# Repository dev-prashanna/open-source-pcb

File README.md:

# Open Source PCB

Open hardware designs for ESP32 robotics, a brushed-motor flight controller, and a USB logic analyser.

## LogicScope S3

[LogicScope S3](LogicScope_S3/) is a compact 8-channel USB digital logic analyser hardware prototype built around the ESP32-S3, with a 55 x 40-mm, two-layer PCB.

- [Project documentation](LogicScope_S3/README.md)
- [KiCad project](LogicScope_S3/LogicScope_S3.kicad_pro)
- [Fabrication and assembly package](LogicScope_S3/fabrication/)
- [Engineering report](LogicScope_S3/docs/Engineering_Report.md)
- [Hardware validation plan](LogicScope_S3/docs/Validation_Plan.md)
- [License](LogicScope_S3/LICENSE)

LS-S3-A0 has recorded passing ERC, DRC, connectivity and schematic/PCB parity checks. Firmware and a simple desktop app v0.1.0 are implemented, with finite DMA captures, an eight-channel viewer, timing cursors and CSV/VCD export. Sampling performance and electrical behavior require physical prototype validation.

- [Firmware: build and flash](LogicScope_S3/firmware/README.md)
- [Desktop app: install and demo](LogicScope_S3/software/README.md)
- [Software verification](LogicScope_S3/docs/Software_Verification.md)

## RoveFlight S3

[RoveFlight S3](RoveFlight_S3/) is a 45 x 45-mm, six-layer ESP32-S3 controller for a 1S brushed quadcopter, with hardware motor interlocks, IMU, barometer, ToF and expansion interfaces.

- [Project documentation](RoveFlight_S3/README.md)
- [KiCad project](RoveFlight_S3/RoveFlight_S3.kicad_pro)
- [Fabrication and assembly package](RoveFlight_S3/fabrication/)
- [Manufacturing readiness and validation](RoveFlight_S3/docs/Manufacturing_Readiness.md)
- [License](RoveFlight_S3/LICENSE)

RF-S3-A0 passes ERC, DRC, connectivity and schematic/PCB parity checks. Via filling/capping and fabricator DFM are required; bench and flight qualification remain open.

## RoveCore One

The complete ESP32 robotics PCB project is in [RoveCore](RoveCore/).

- [Project documentation](RoveCore/README.md)
- [KiCad project](RoveCore/RoveCore_One.kicad_pro)
- [Fabrication files](RoveCore/fabrication/)
- [Manufacturing readiness](RoveCore/docs/Manufacturing_Readiness.md)
- [License](RoveCore/LICENSE)

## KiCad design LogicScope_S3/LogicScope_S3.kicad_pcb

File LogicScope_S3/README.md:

# LogicScope S3 — LS-S3-A0

Compact 8-channel USB digital logic analyzer hardware by Prashanna Tiwari.
Open `LogicScope_S3.kicad_pro` in KiCad 10. The project contains native
hierarchical schematics, verified library parts and an actual two-layer PCB.

**Engineering prototype; firmware and desktop software v0.1.0 are implemented
but not bench validated.** 1 MS/s is an unmeasured finite-capture target,
not an advertised continuous rate. There is no analog voltage measurement.

## Design

- ESP32-S3-WROOM-1-N8R2, eight parallel LCD_CAM inputs and GDMA.
- SN74LVC245APW at 3.3 V with 5.5-V-tolerant inputs, 220-ohm series resistors
  and 100-kilohm input pull-downs. External signal range: 0–5 V.
- USB-C device port, native USB Full-Speed, ESD protection and 3.3-V buck supply.
- Two 2x5 input headers, BOOT/RESET, capture/power LEDs and UART/test access.
- 55 x 40 mm, two layers, 0.8-mm board; PCB antenna overhangs by 6.75 mm.
- **TIWARI** etched in front copper and printed on silkscreen.

Use a common ground with the target. J2 pin 7 is a current-limited reference
only; this instrument does not power the target.

## Firmware and desktop software

- [ESP32-S3 firmware: build, flash and capture behavior](firmware/README.md)
- [Simple desktop app: setup and usage](software/README.md)
- [USB protocol](docs/USB_Protocol.md)
- [Software verification and remaining hardware checks](docs/Software_Verification.md)

Firmware uses LCD_CAM/GDMA with the PCB's GPIO12-to-GPIO11 sampling-clock
loopback. Select 100 kS/s, 250 kS/s, 500 kS/s or 1 MS/s and collect up to
65,536 packed eight-channel samples before uploading over USB. All rates
remain unmeasured. Trigger search marks a matching event within a finite
capture; rolling pre-trigger history and continuous streaming are not enabled.

The Python/Tk app includes eight waveform lanes, zoom/pan, timing cursors,
save/open, CSV/VCD export, and a synthetic demo mode. From `software/`:

```sh
python3 -m venv .venv
. .venv/bin/activate
python -m pip install -e .
logicscope --demo
```

## Files and limitations

Read [acquisition architecture](docs/Acquisition_Architecture.md),
[electrical/fabrication decisions](docs/Electrical_and_Fabrication.md) and the
[hardware validation plan](docs/Validation_Plan.md) before ordering or using
a prototype. Connector pinout and GPIO allocation are supplied as CSV files.
`BOM.csv` contains exact manufacturer part numbers and DNP status.

Final checks: ERC 0, DRC 0, unconnected nets 0, schematic parity findings 0.
Read the [engineering report](docs/Engineering_Report.md). Manufacturing files
are in `fabrication/`; the KiCad 3D render is in `previews/`.

Fabrication needs a stack-specific USB impedance review and the documented
USB connector hole-clearance capability. Sampling, USB throughput, power,
thermal and ESD behavior require physical prototype testing.

## Tool workflow

Connected KiCad MCP created the native project and initial components,
generated a netlist and ran electrical checks. Native pcbnew scripts perform
placement and routing because those editing operations are absent from the
connected MCP. Native KiCad CLI and MCP perform final validation and exports.
Scripts under `scripts/` record engineering operations; do not run placement
or initial-routing scripts over the completed board. `release.py`, when
available, validates the current design and exports without reconstructing it.

Copyright (c) 2026 Prashanna Tiwari. Hardware: [CERN-OHL-P-2.0](LICENSE).
Firmware and desktop app: MIT (see their respective directories).
KiCad-derived library graphics retain their upstream licence in `libraries/`.

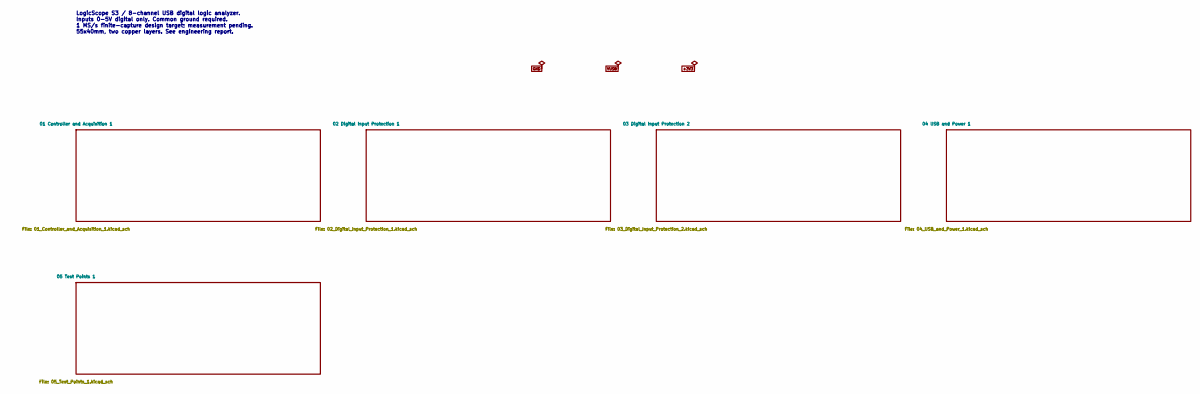
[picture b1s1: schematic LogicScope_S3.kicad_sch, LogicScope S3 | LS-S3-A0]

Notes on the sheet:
LogicScope S3 / 8-channel USB digital logic analyzer. Inputs 0-5V digital only. Common ground required. 1 MS/s finite-capture design target; measurement pending. 55x40mm, two copper layers. See engineering report.

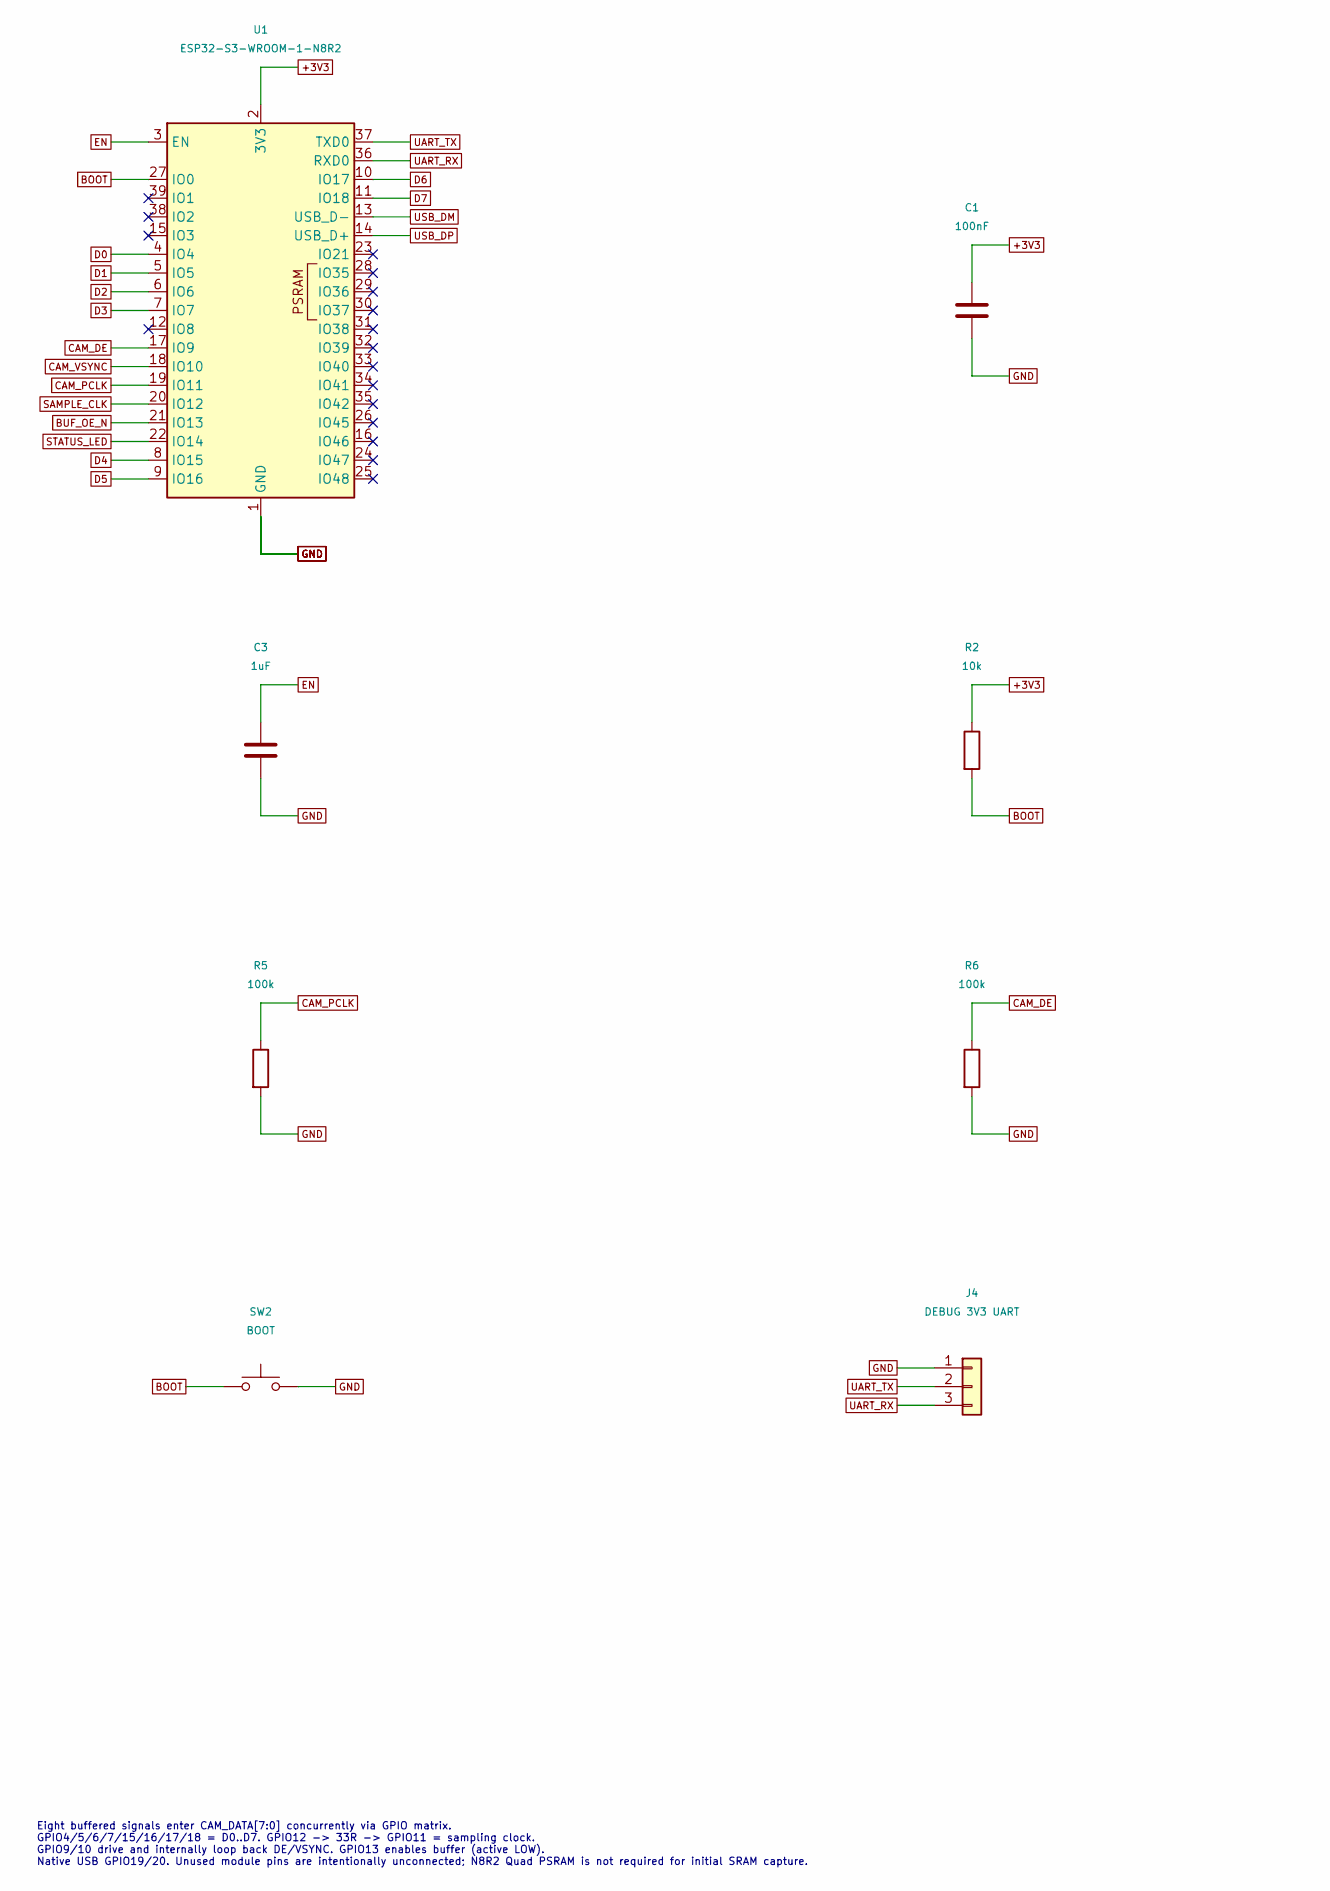
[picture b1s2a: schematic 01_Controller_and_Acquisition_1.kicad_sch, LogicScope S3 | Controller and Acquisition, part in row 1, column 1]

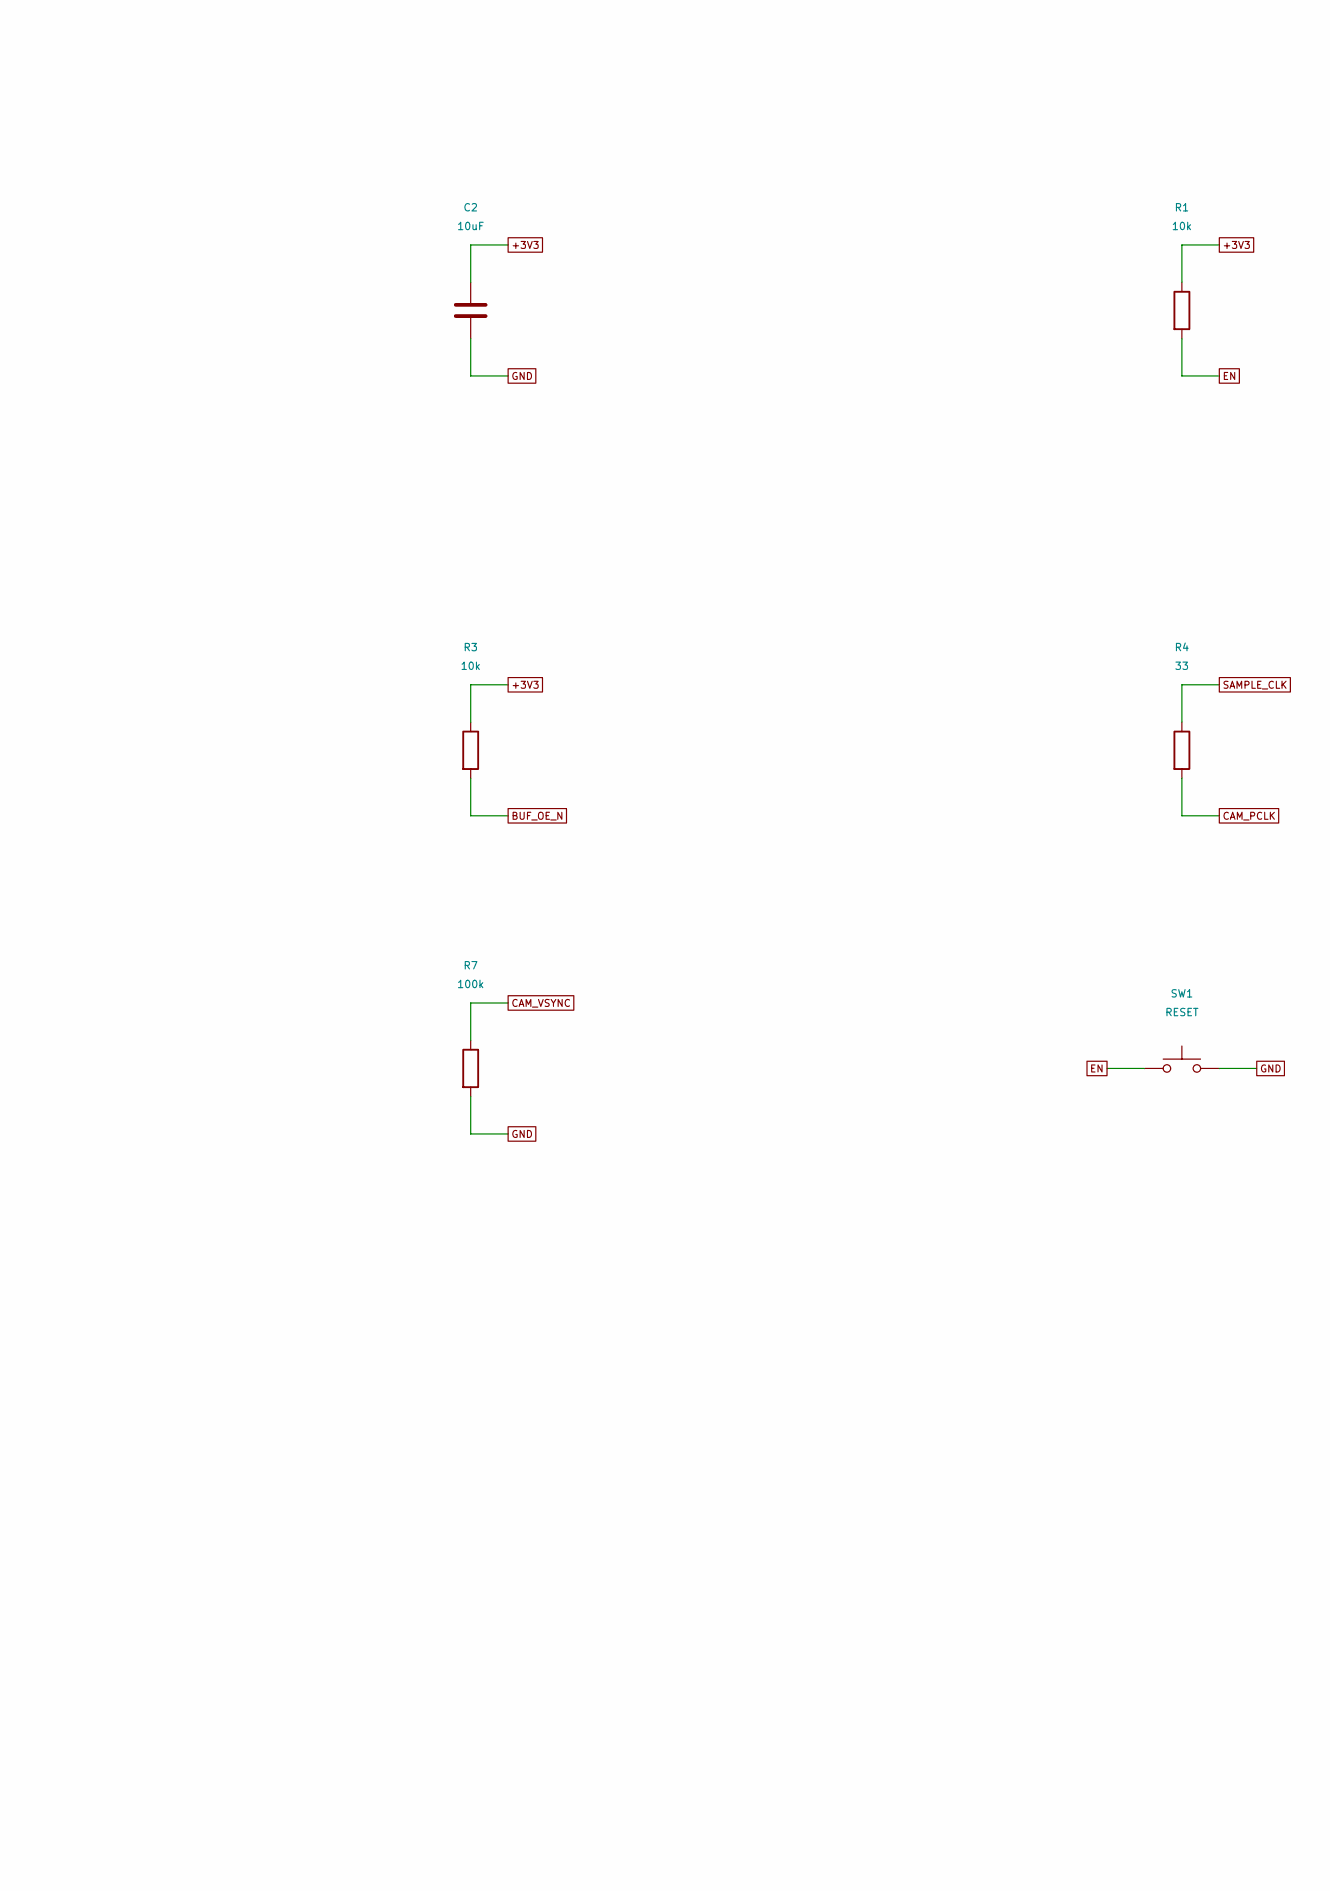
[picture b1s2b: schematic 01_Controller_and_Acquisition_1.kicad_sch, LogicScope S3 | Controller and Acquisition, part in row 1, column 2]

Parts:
C1: 100nF; C_0603_1608Metric; MPN GRM188R71C104KA01D
C2: 10uF; C_0805_2012Metric; MPN GRM21BR61A106KE19L
C3: 1uF; C_0603_1608Metric; MPN GRM188R61A105KA61D
J4: DEBUG 3V3 UART; PinHeader_1x03_P2.54mm_Vertical; MPN 61300311121
R1, R2, R3: 10k; R_0603_1608Metric; MPN RC0603FR-0710KL
R4: 33; R_0603_1608Metric; MPN RC0603FR-0733RL
R5, R6, R7: 100k; R_0603_1608Metric; MPN RC0603FR-07100KL
SW1: RESET; SW_Push_1P1T-SH_NO_CK_KMR2xxG; MPN KMR221GLFS
SW2: BOOT; SW_Push_1P1T-SH_NO_CK_KMR2xxG; MPN KMR221GLFS
U1: ESP32-S3-WROOM-1-N8R2; ESP32-S3-WROOM-1_Overhang; MPN ESP32-S3-WROOM-1-N8R2

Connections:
+3V3: C1.1, C2.1, R1.1, R2.1, R3.1, U1.2 (3V3); also elsewhere on the board
BOOT: R2.2, SW2.1, U1.27 (IO0)
BUF_OE_N: R3.2, U1.21 (IO13); also elsewhere on the board
CAM_DE: R6.1, U1.17 (IO9); also elsewhere on the board
CAM_PCLK: R4.2, R5.1, U1.19 (IO11); also elsewhere on the board
CAM_VSYNC: R7.1, U1.18 (IO10); also elsewhere on the board
D0: U1.4 (IO4); also elsewhere on the board
D1: U1.5 (IO5); also elsewhere on the board
D2: U1.6 (IO6); also elsewhere on the board
D3: U1.7 (IO7); also elsewhere on the board
D4: U1.8 (IO15); also elsewhere on the board
D5: U1.9 (IO16); also elsewhere on the board
D6: U1.10 (IO17); also elsewhere on the board
D7: U1.11 (IO18); also elsewhere on the board
EN: C3.1, R1.2, SW1.1, U1.3 (EN); also elsewhere on the board
GND: C1.2, C2.2, C3.2, J4.1, R5.2, R6.2, R7.2, SW1.2, SW2.2, U1.1 (GND), U1.40 (GND), U1.41 (GND); also elsewhere on the board
SAMPLE_CLK: R4.1, U1.20 (IO12)
STATUS_LED: U1.22 (IO14); also elsewhere on the board
UART_RX: J4.3, U1.36 (RXD0)
UART_TX: J4.2, U1.37 (TXD0)
USB_DM: U1.13 (USB_D-); also elsewhere on the board
USB_DP: U1.14 (USB_D+); also elsewhere on the board

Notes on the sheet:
Eight buffered signals enter CAM_DATA[7:0] concurrently via GPIO matrix. GPIO4/5/6/7/15/16/17/18 = D0..D7. GPIO12 -> 33R -> GPIO11 = sampling clock. GPIO9/10 drive and internally loop back DE/VSYNC. GPIO13 enables buffer (active LOW). Native USB GPIO19/20. Unused module pins are intentionally uncon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

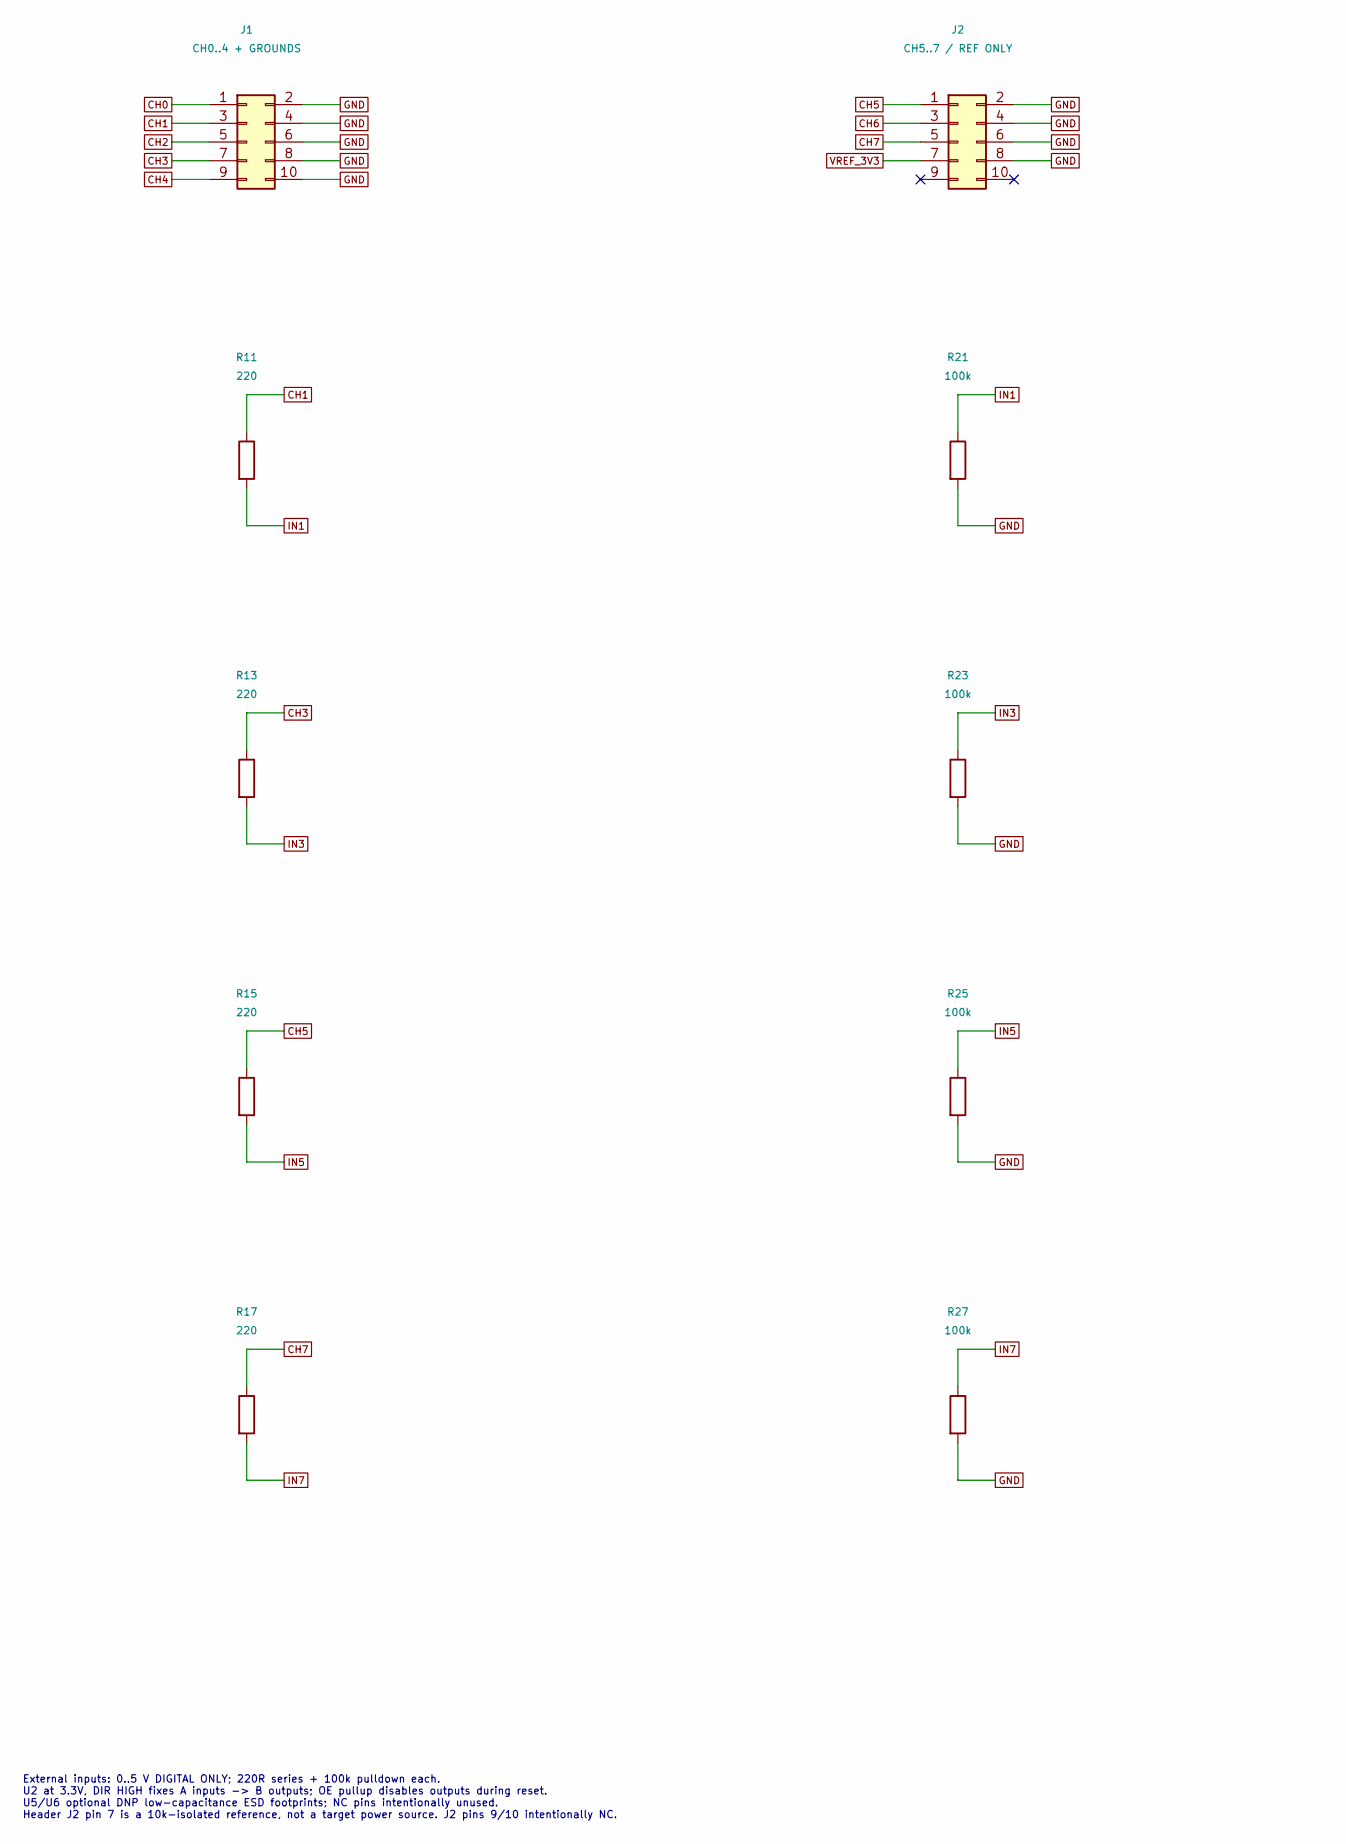
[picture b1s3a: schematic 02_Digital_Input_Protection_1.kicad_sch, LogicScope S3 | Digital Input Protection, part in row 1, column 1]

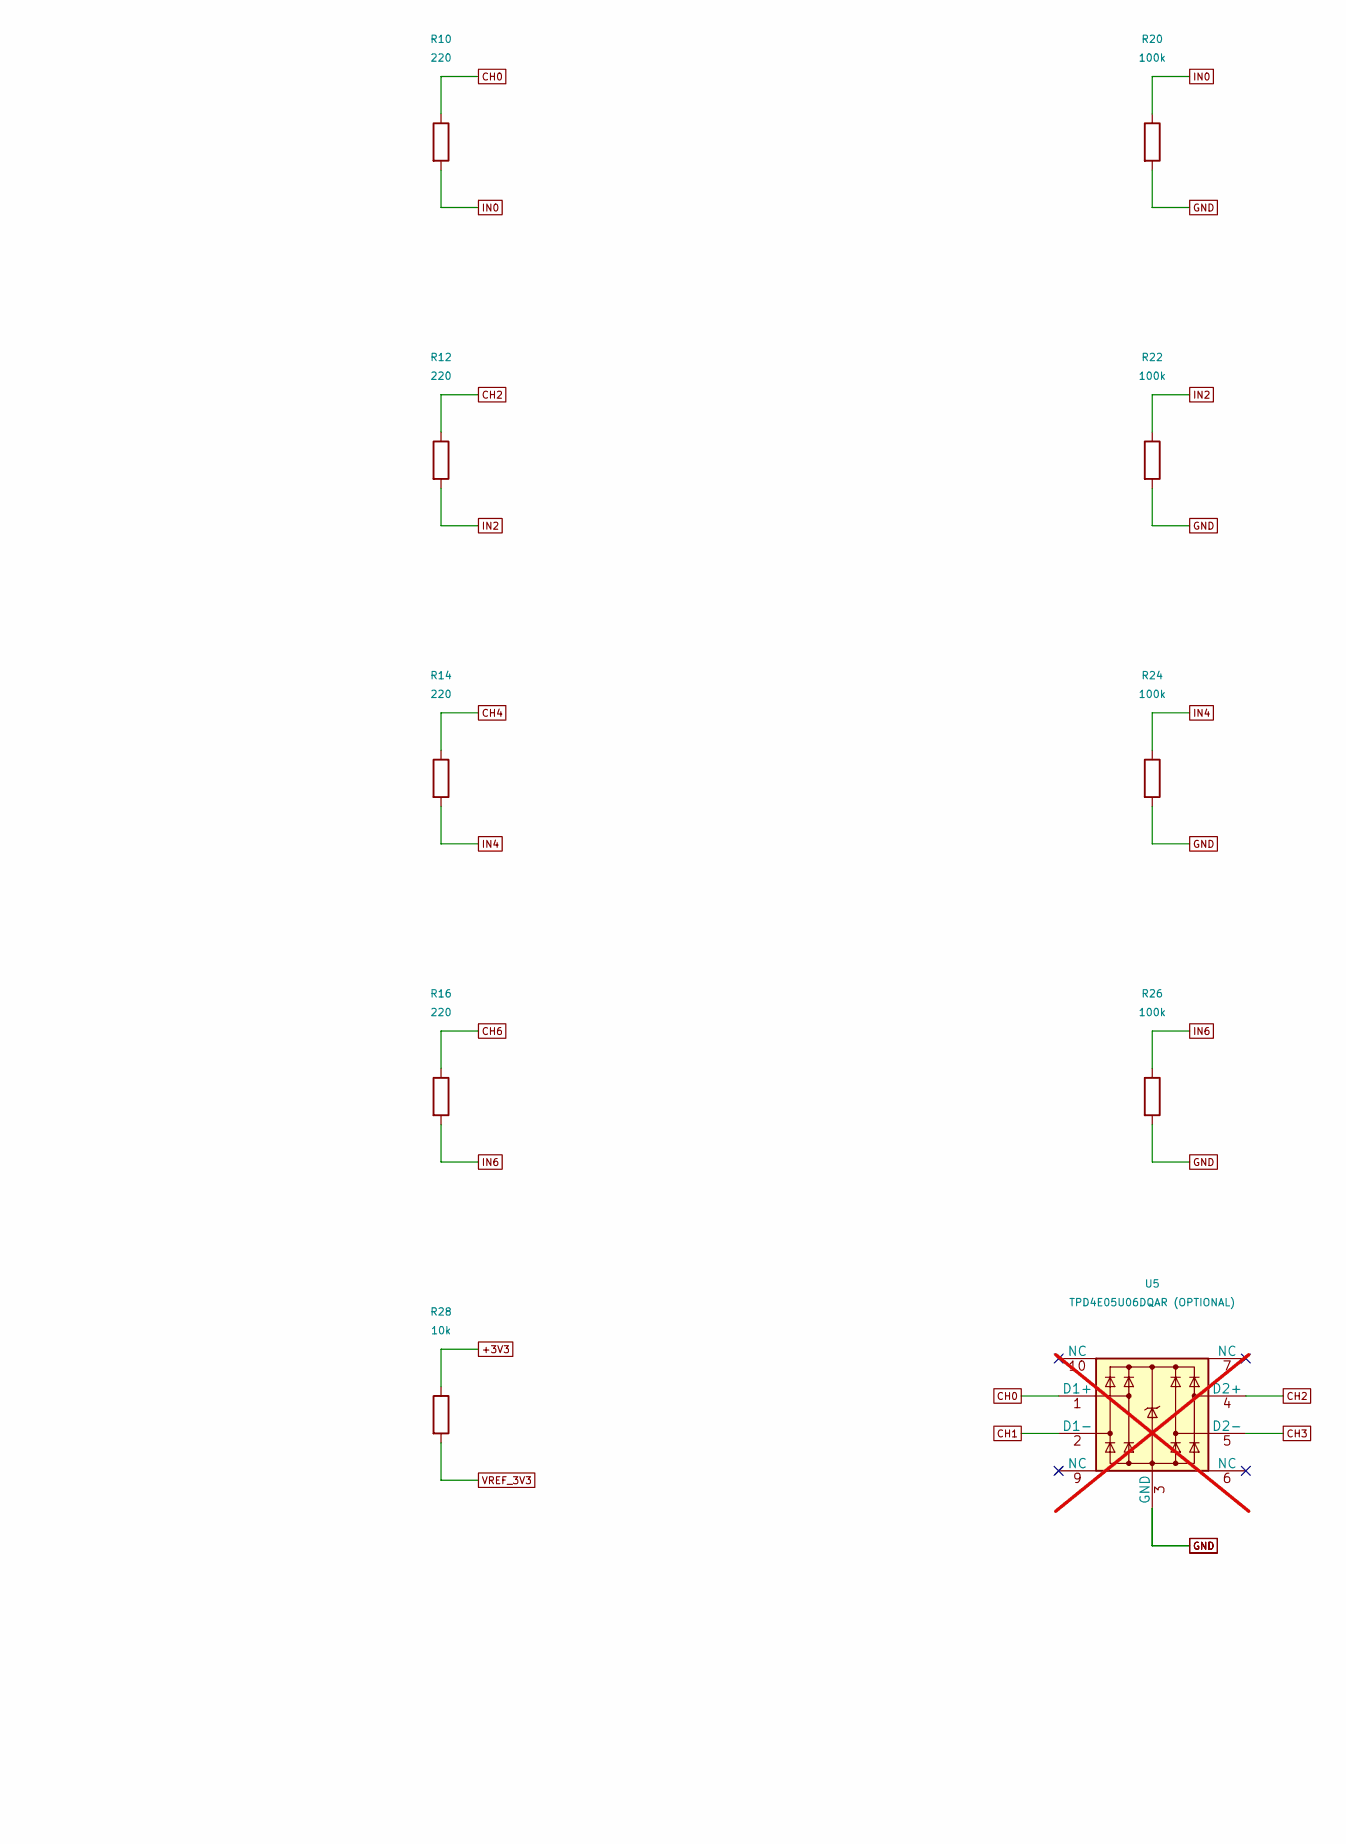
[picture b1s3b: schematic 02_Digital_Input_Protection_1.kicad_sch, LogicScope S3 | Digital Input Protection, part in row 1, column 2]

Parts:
J1: CH0..4 + GROUNDS; PinHeader_2x05_P2.54mm_Vertical; MPN 61301021121
J2: CH5..7 / REF ONLY; PinHeader_2x05_P2.54mm_Vertical; MPN 61301021121
R10, R11, R12, R13, R14, R15, R16, R17: 220; R_0603_1608Metric; MPN RC0603FR-07220RL
R20, R21, R22, R23, R24, R25, R26, R27: 100k; R_0603_1608Metric; MPN RC0603FR-07100KL
R28: 10k; R_0603_1608Metric; MPN RC0603FR-0710KL
U5: TPD4E05U06DQAR (OPTIONAL); USON-10_2.5x1.0mm_P0.5mm; MPN TPD4E05U06DQAR; not fitted

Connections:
+3V3: R28.1; also elsewhere on the board
CH0: J1.1, R10.1, U5.1 (D1+)
CH1: J1.3, R11.1, U5.2 (D1-)
CH2: J1.5, R12.1, U5.4 (D2+)
CH3: J1.7, R13.1, U5.5 (D2-)
CH4: J1.9, R14.1; also elsewhere on the board
CH5: J2.1, R15.1; also elsewhere on the board
CH6: J2.3, R16.1; also elsewhere on the board
CH7: J2.5, R17.1; also elsewhere on the board
GND: J1.2, J1.4, J1.6, J1.8, J1.10, J2.2, J2.4, J2.6, J2.8, R20.2, R21.2, R22.2, R23.2, R24.2, R25.2, R26.2, R27.2, U5.3 (GND), U5.8 (GND); also elsewhere on the board
IN0: R10.2, R20.1; also elsewhere on the board
IN1: R11.2, R21.1; also elsewhere on the board
IN2: R12.2, R22.1; also elsewhere on the board
IN3: R13.2, R23.1; also elsewhere on the board
IN4: R14.2, R24.1; also elsewhere on the board
IN5: R15.2, R25.1; also elsewhere on the board
IN6: R16.2, R26.1; also elsewhere on the board
IN7: R17.2, R27.1; also elsewhere on the board
VREF_3V3: J2.7, R28.2

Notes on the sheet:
External inputs: 0..5 V DIGITAL ONLY; 220R series + 100k pulldown each. U2 at 3.3V, DIR HIGH fixes A inputs -> B outputs; OE pullup disables outputs during reset. U5/U6 optional DNP low-capacitance ESD footprints; NC pins intentionally unused. Header J2 pin 7 is a 10k-isolated reference, not a targ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

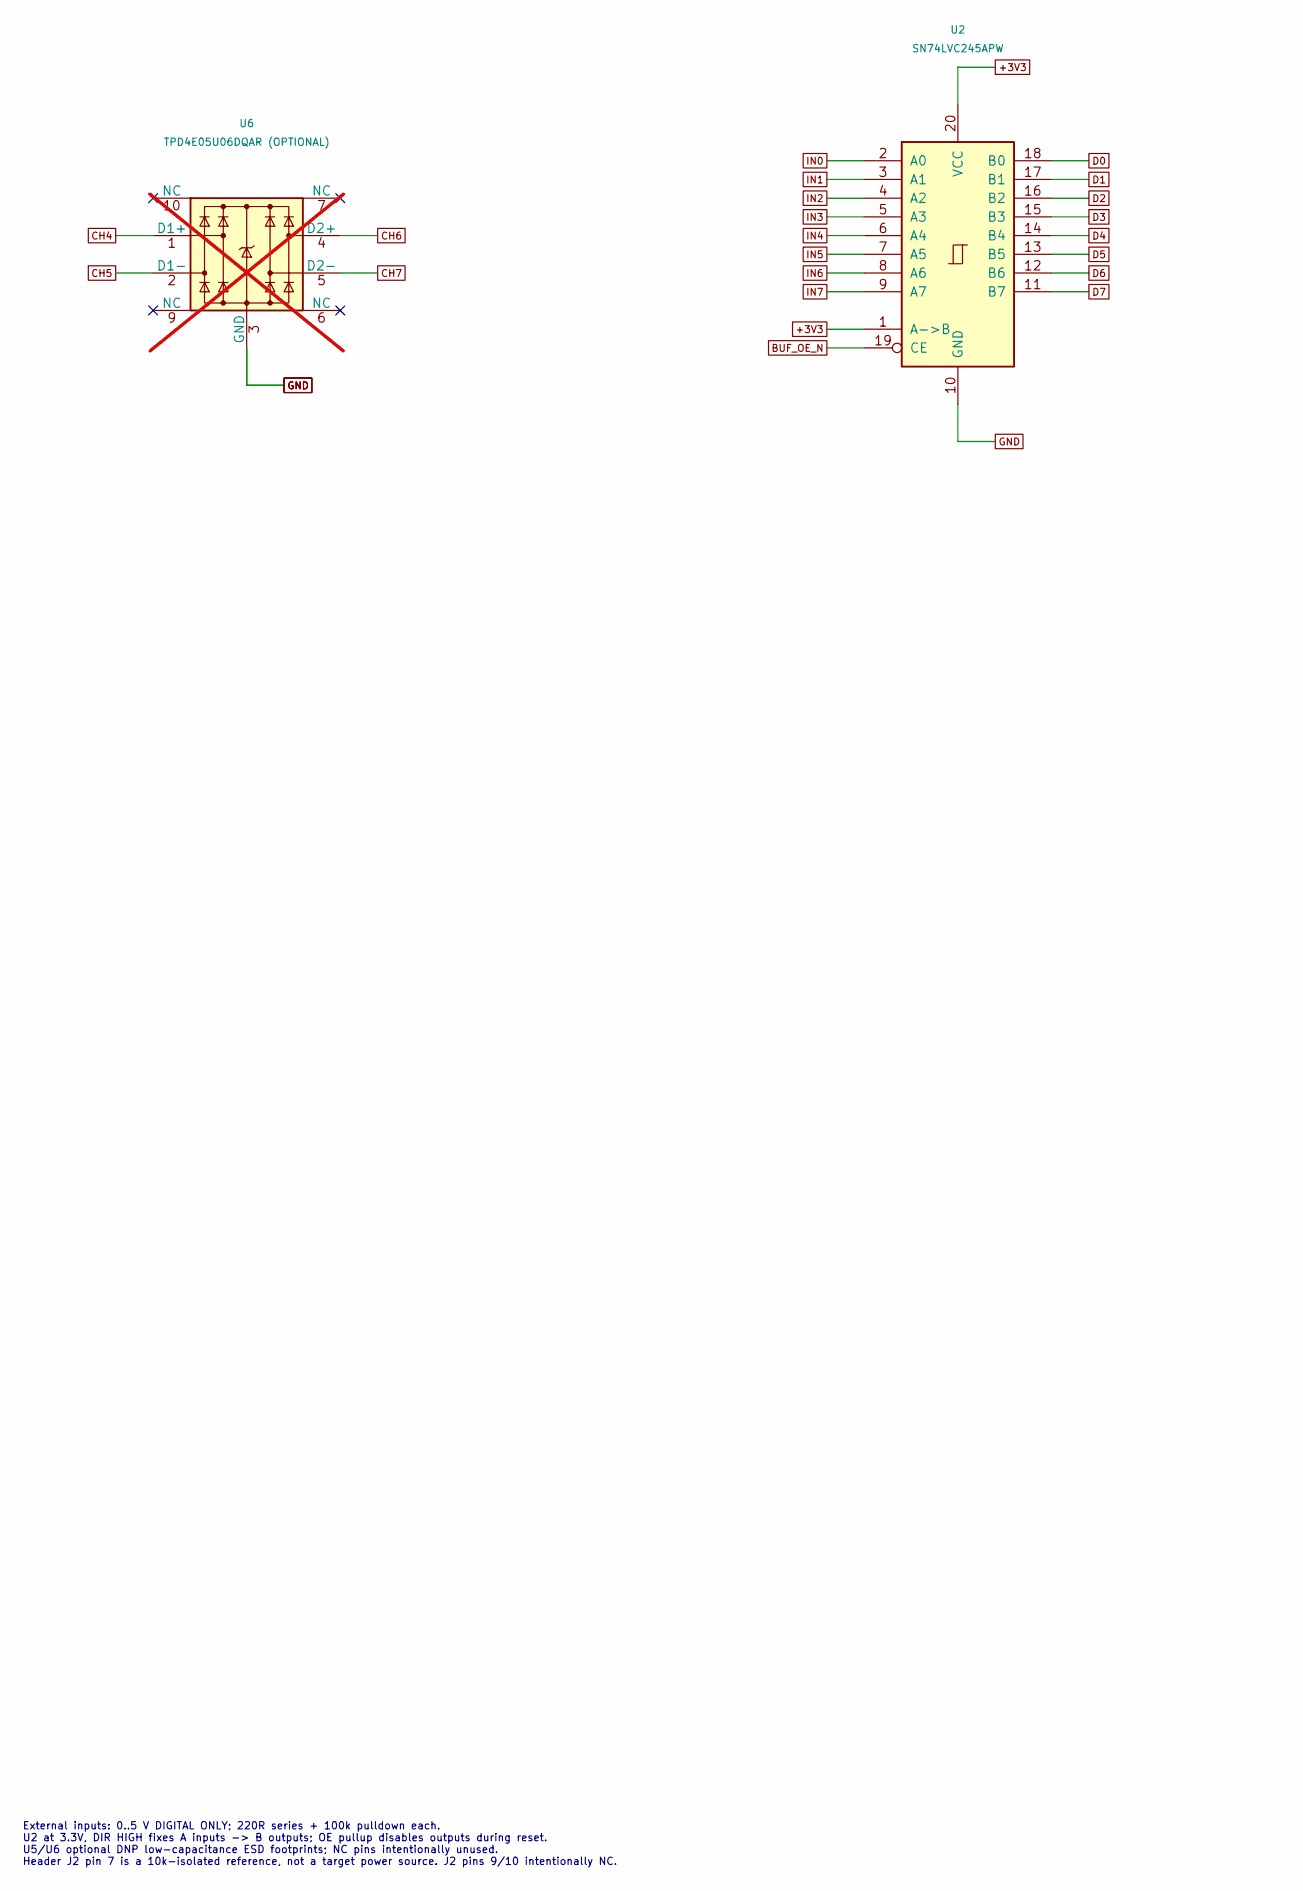
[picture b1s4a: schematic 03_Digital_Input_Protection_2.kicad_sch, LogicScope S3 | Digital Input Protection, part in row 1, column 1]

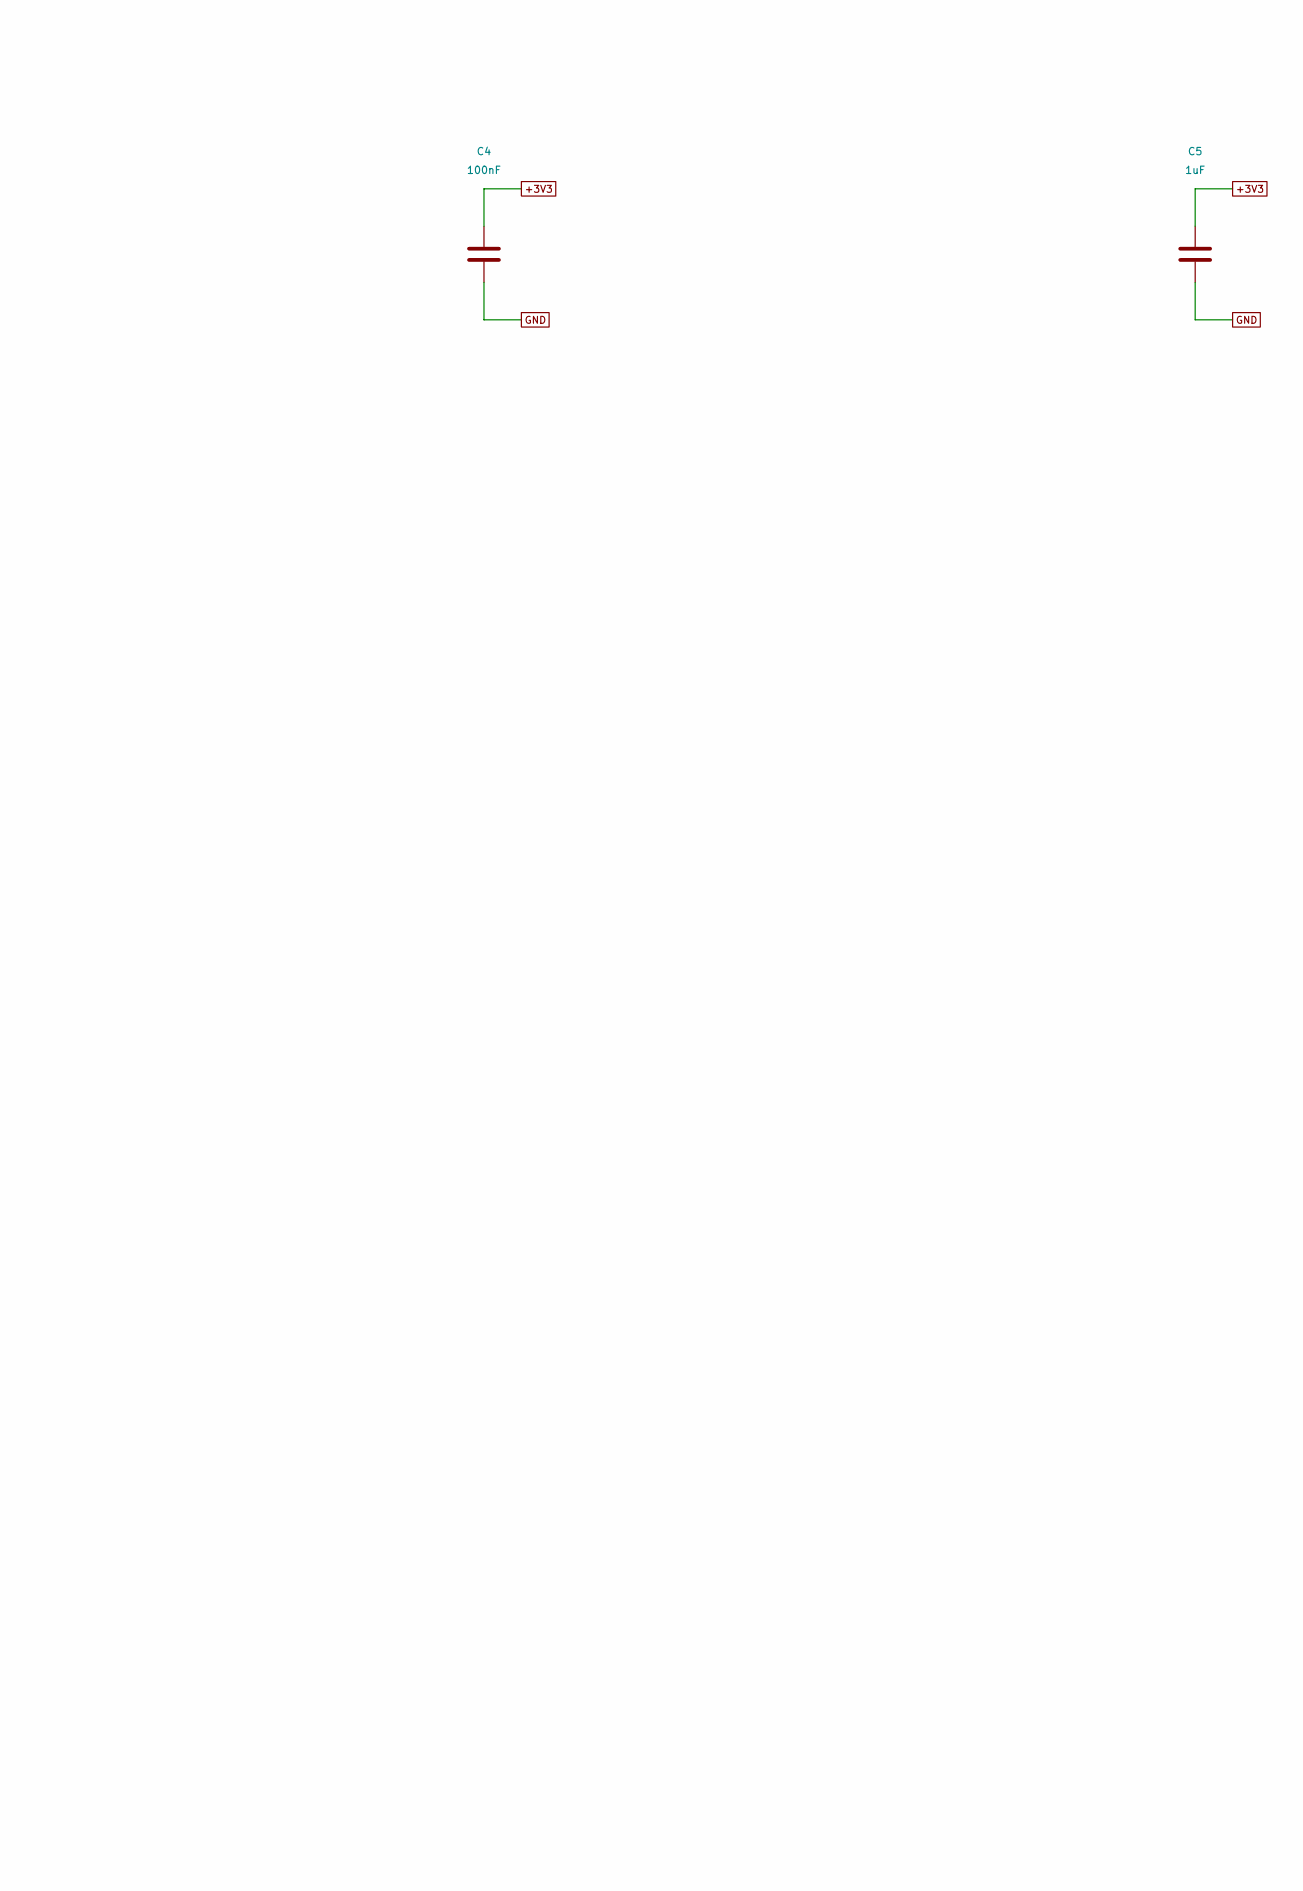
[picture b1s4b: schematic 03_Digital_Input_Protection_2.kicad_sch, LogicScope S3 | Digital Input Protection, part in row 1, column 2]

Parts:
C4: 100nF; C_0603_1608Metric; MPN GRM188R71C104KA01D
C5: 1uF; C_0603_1608Metric; MPN GRM188R61A105KA61D
U2: SN74LVC245APW; TSSOP-20_4.4x6.5mm_P0.65mm; MPN SN74LVC245APW
U6: TPD4E05U06DQAR (OPTIONAL); USON-10_2.5x1.0mm_P0.5mm; MPN TPD4E05U06DQAR; not fitted

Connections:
+3V3: C4.1, C5.1, U2.1 (A->B), U2.20 (VCC); also elsewhere on the board
BUF_OE_N: U2.19 (CE); also elsewhere on the board
CH4: U6.1 (D1+); also elsewhere on the board
CH5: U6.2 (D1-); also elsewhere on the board
CH6: U6.4 (D2+); also elsewhere on the board
CH7: U6.5 (D2-); also elsewhere on the board
D0: U2.18 (B0); also elsewhere on the board
D1: U2.17 (B1); also elsewhere on the board
D2: U2.16 (B2); also elsewhere on the board
D3: U2.15 (B3); also elsewhere on the board
D4: U2.14 (B4); also elsewhere on the board
D5: U2.13 (B5); also elsewhere on the board
D6: U2.12 (B6); also elsewhere on the board
D7: U2.11 (B7); also elsewhere on the board
GND: C4.2, C5.2, U2.10 (GND), U6.3 (GND), U6.8 (GND); also elsewhere on the board
IN0: U2.2 (A0); also elsewhere on the board
IN1: U2.3 (A1); also elsewhere on the board
IN2: U2.4 (A2); also elsewhere on the board
IN3: U2.5 (A3); also elsewhere on the board
IN4: U2.6 (A4); also elsewhere on the board
IN5: U2.7 (A5); also elsewhere on the board
IN6: U2.8 (A6); also elsewhere on the board
IN7: U2.9 (A7); also elsewhere on the board

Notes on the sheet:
External inputs: 0..5 V DIGITAL ONLY; 220R series + 100k pulldown each. U2 at 3.3V, DIR HIGH fixes A inputs -> B outputs; OE pullup disables outputs during reset. U5/U6 optional DNP low-capacitance ESD footprints; NC pins intentionally unused. Header J2 pin 7 is a 10k-isolated reference, not a targ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
